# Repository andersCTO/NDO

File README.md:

# NDO

## Installation for development
1. Create a ROS2 workspace or use [NDO workspace for VSCode](https://github.com/JPDF/vscode_ndo_ros2_ws).
2. Copy this repo to your workspace. Your workspace should now look like this:
```
workspace
└──src
    └──ndo <-- THIS REPO
       │  README.md
       │  ...
       └──ndo
       └──ndo_description
       └──ndo_nav
       └──ndo_teleop
```
3. Install dependencies `rosdep install --from-paths src --ignore-src -y`
4. Build project `colcon build`

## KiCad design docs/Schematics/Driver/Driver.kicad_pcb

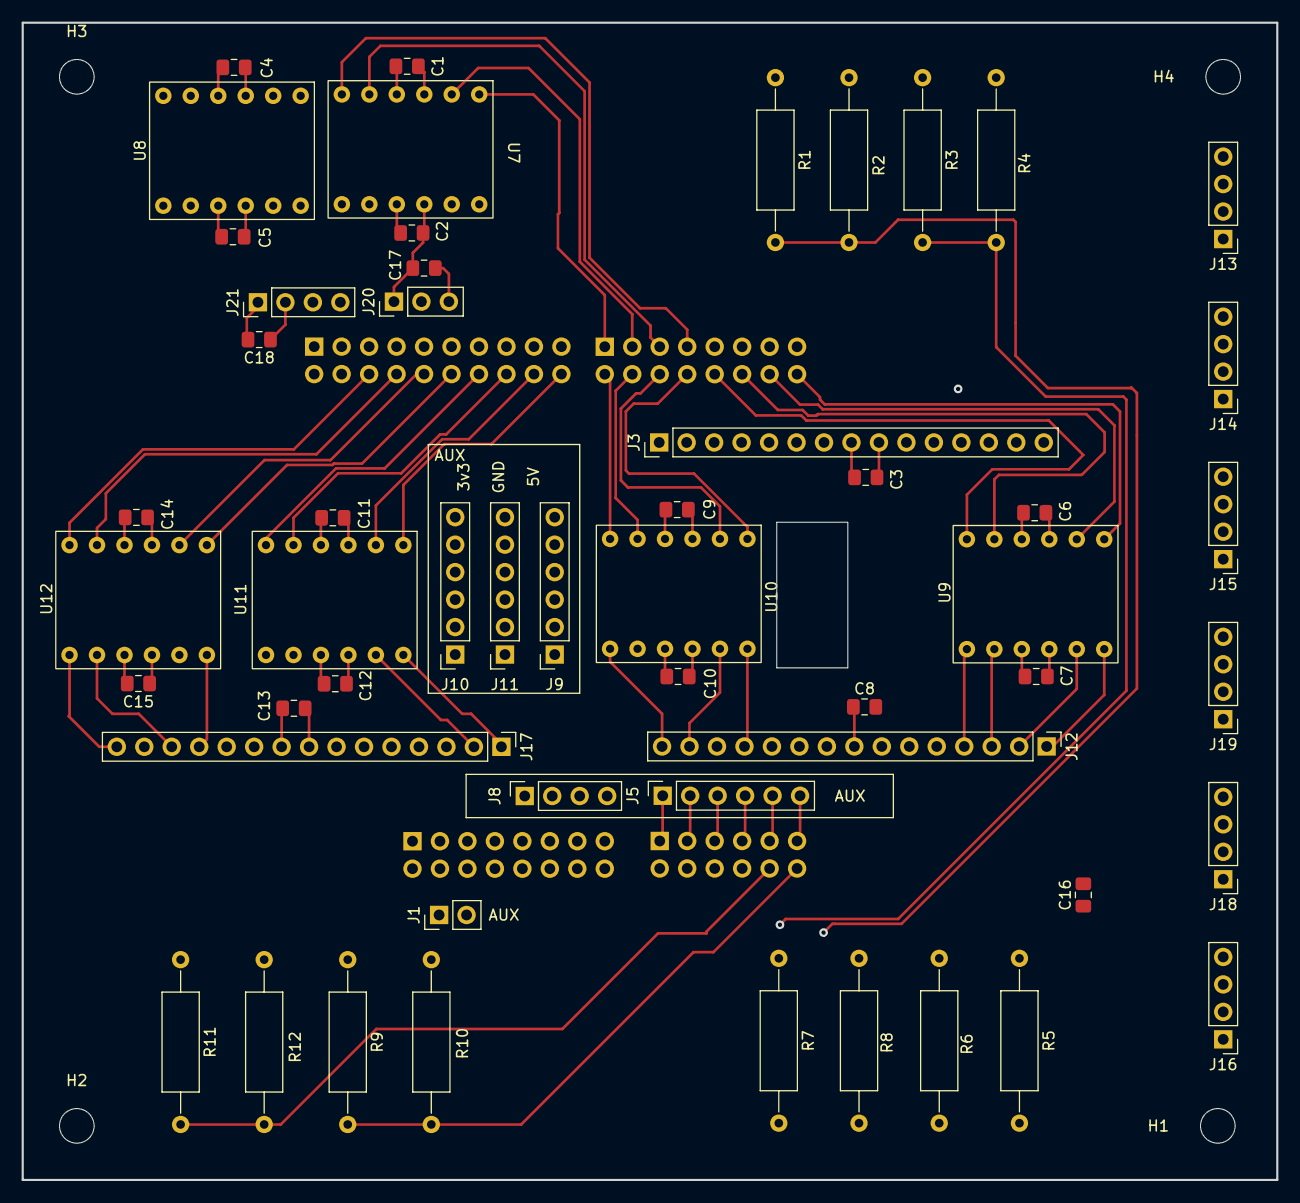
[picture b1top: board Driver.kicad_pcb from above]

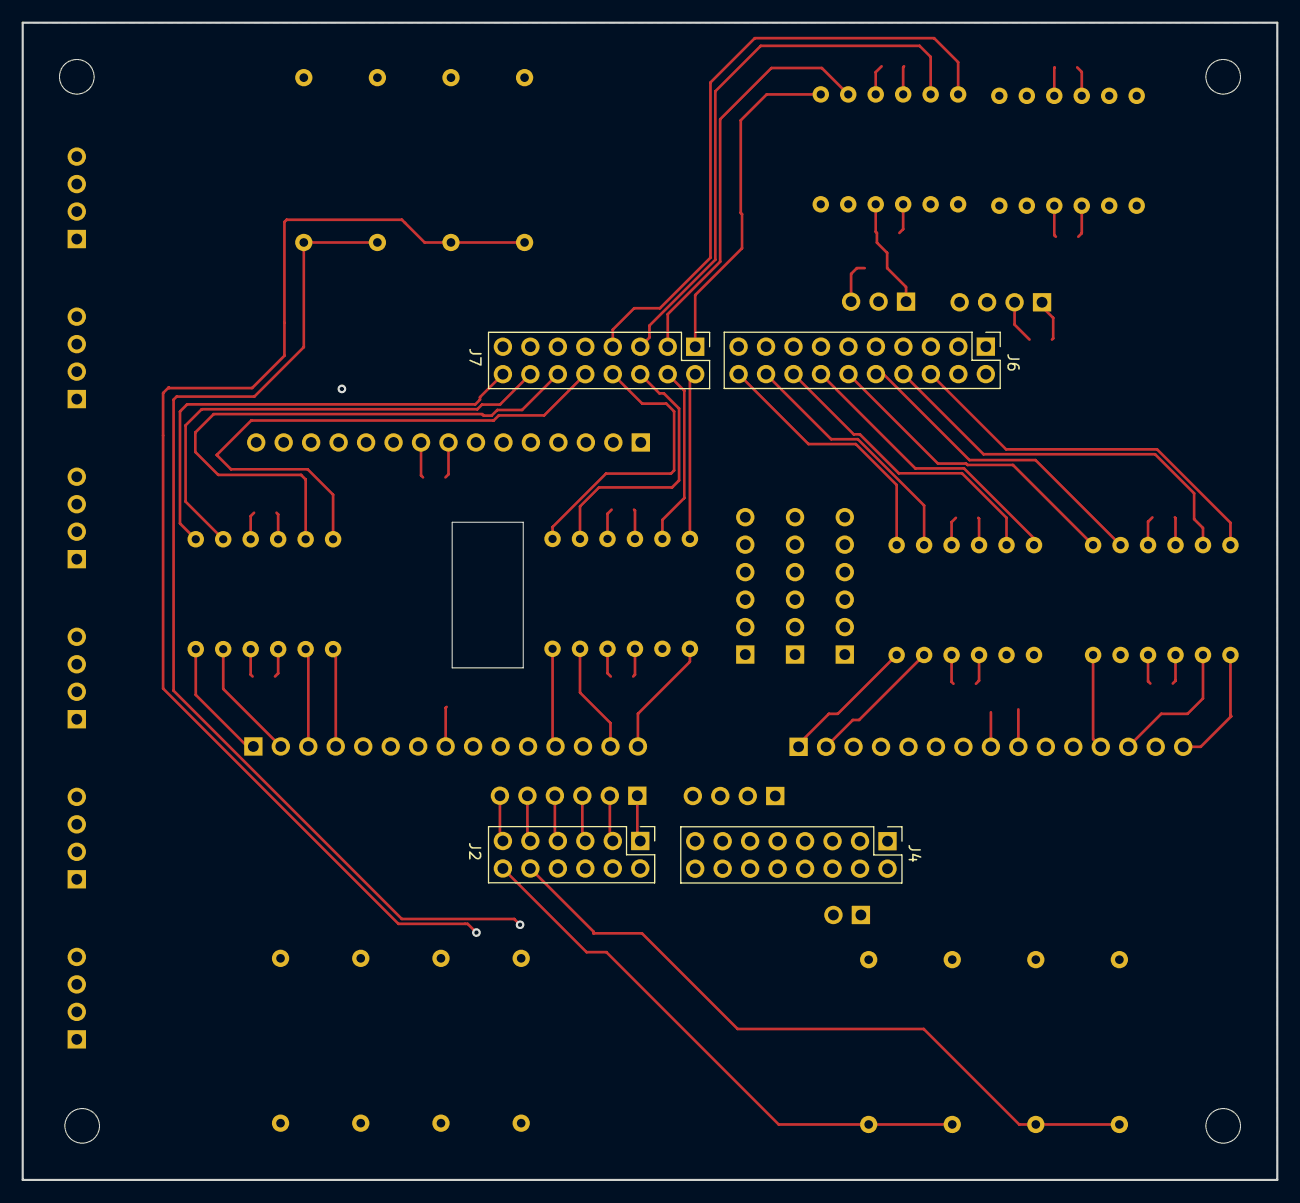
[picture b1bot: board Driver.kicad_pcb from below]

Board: 4 copper layers, 116.0 x 107.0 mm, 61 parts (4 on the bottom side), 83 nets.

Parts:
C1, C2, C3, C4, C5, C6, C7, C8, C9, C10, C11, C12, C13, C14, C15, C16, C17, C18: C_Polarized; C_0805_2012Metric_Pad1.18x1.45mm_HandSolder
H1, H2, H3, H4: MountingHole; MountingHole_3.2mm_M3
J1: AUX_IOref; PinHeader_1x02_P2.54mm_Vertical
J2: PH_Ain; PinHeader_2x06_P2.54mm_Vertical
J3, J12, J17: PH_MC; PinHeader_1x15_P2.54mm_Vertical
J4: PH_PWR; PinHeader_2x08_P2.54mm_Vertical
J5: AUX_AIO; PinSocket_1x06_P2.54mm_Vertical
J6: PH_IO1; PinHeader_2x10_P2.54mm_Vertical
J7: PH_IO2; PinHeader_2x08_P2.54mm_Vertical
J8: AUX_Ain; PinSocket_1x04_P2.54mm_Vertical
J9: AUX_5V; PinSocket_1x06_P2.54mm_Vertical
J10: AUX_3V3; PinSocket_1x06_P2.54mm_Vertical
J11: AUX_GND; PinSocket_1x06_P2.54mm_Vertical
J13: A1363xKTTN-1_front_left; PinHeader_1x04_P2.54mm_Vertical
J14: A1363xKTTN-1_midle_left; PinHeader_1x04_P2.54mm_Vertical
J15: A1363xKTTN-1_rear_left; PinHeader_1x04_P2.54mm_Vertical
J16: A1363xKTTN-1_front_right; PinHeader_1x04_P2.54mm_Vertical
J18: A1363xKTTN-1_midle_right; PinHeader_1x04_P2.54mm_Vertical
J19: A1363xKTTN-1_rear_right; PinHeader_1x04_P2.54mm_Vertical
J20: PH_HBT; PinHeader_1x03_P2.54mm_Vertical
J21: PH_I2C; PinHeader_1x04_P2.54mm_Vertical
R1, R2, R3, R4, R5, R6, R7, R8, R9, R10, R11, R12: R; R_Axial_DIN0309_L9.0mm_D3.2mm_P15.24mm_Horizontal
U7, U8, U9, U10, U11, U12: 4_channel_lvl_converter_Art.nr:_41017630; 4ch_level_shifter_Artnr_ 41017630

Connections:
+3.3V: C1.1, C4.1, C6.1, C9.1, C11.1, C14.1, C16.1, J4.8, J10.1, J10.2, J10.3, J10.4, J10.5, J10.6, J13.1, J14.1, J15.1, J16.1, J18.1, J19.1, U7.3 (3v3), U8.3 (3v3), U9.3 (3v3), U10.3 (3v3), U11.3 (3v3), U12.3 (3v3)
+5V: C2.1, C3.1, C5.1, C7.1, C8.1, C10.1, C12.1, C13.1, C15.1, C17.1, C18.1, J3.8, J4.10, J9.1, J9.2, J9.3, J9.4, J9.5, J9.6, J12.8, J17.8, J20.1, J21.2, U7.10 (5V), U8.10 (5V), U9.10 (5V), U10.10 (5V), U11.10 (5V), U12.10 (5V)
/Arty Z7/IOREF: J1.1, J4.4
/Arty Z7/RST: J1.2, J4.6
/Arty Z7/XVREF: J4.15, J8.4
/Arty Z7/v_n: J4.11, J8.2
/Arty Z7/v_p: J4.9, J8.1
/FLENC: J6.19, J13.2
/FRENC: J6.17, J16.2
/HeartBeat: J6.5, J20.2
/MFL/CS: J2.2, R1.2, R2.1
/MFL/EN: J7.1, U7.1 (LV1)
/MFL/INA: J7.3, U7.2 (LV2)
/MFL/INB: J7.5, U7.5 (LV3)
/MFL/PWM: J7.7, U7.6 (LV4)
/MFR/CS: J2.4, R3.2, R4.1
/MFR/EN: J7.15, U8.6 (LV4)
/MFR/INA: J7.13, U8.5 (LV3)
/MFR/INB: J7.11, U8.2 (LV2)
/MFR/PWM: J7.9, U8.1 (LV1)
/MLENC: J6.15, J14.2
/MML/EN: J7.16, U9.1 (LV1)
/MML/INA: J7.14, U9.2 (LV2)
/MML/INB: J7.12, U9.5 (LV3)
/MML/PWM: J7.10, U9.6 (LV4)
/MMR/CS: J2.6, R7.2, R8.1
/MMR/EN: J7.2, U10.6 (LV4)
/MMR/INA: J7.4, U10.5 (LV3)
/MMR/INB: J7.6, U10.2 (LV2)
/MMR/PWM: J7.8, U10.1 (LV1)
/MRENC: J6.13, J18.2
/MRL/CS: J2.12, R9.2, R10.1
/MRL/EN: J6.20, U11.1 (LV1)
/MRL/INA: J6.18, U11.2 (LV2)
/MRL/INB: J6.16, U11.5 (LV3)
/MRL/PWM: J6.14, U11.6 (LV4)
/MRR/CS: J2.10, R11.2, R12.1
/MRR/EN: J6.6, U12.6 (LV4)
/MRR/INB: J6.10, U12.2 (LV2)
/MRR/PWM: J6.12, U12.1 (LV1)
/MR/INA: J6.8, U12.5 (LV3)
/MWL/CS: J2.8, R5.2, R6.1
/Motor Driver Front/Dual_VNH3SP30/1CS: J3.5, R1.1
/Motor Driver Front/Dual_VNH3SP30/1DIAG/EN: J3.1, U7.12 (HV1)
/Motor Driver Front/Dual_VNH3SP30/1INA: J3.2, U7.11 (HV2)
/Motor Driver Front/Dual_VNH3SP30/1INB: J3.3, U7.8 (HV3)
/Motor Driver Front/Dual_VNH3SP30/1PWM: J3.4, U7.7 (HV4)
/Motor Driver Front/Dual_VNH3SP30/2CS: J3.11, R3.1
/Motor Driver Front/Dual_VNH3SP30/2DIAG/EN: J3.15, U8.7 (HV4)
/Motor Driver Front/Dual_VNH3SP30/2INA: J3.13, U8.8 (HV3)
/Motor Driver Front/Dual_VNH3SP30/2INB: J3.14, U8.11 (HV2)
/Motor Driver Front/Dual_VNH3SP30/2PWM: J3.12, U8.12 (HV1)
/Motor Driver Midle/Dual_VNH3SP30/1CS: J12.5, R5.1
/Motor Driver Midle/Dual_VNH3SP30/1DIAG/EN: J12.1, U9.12 (HV1)
/Motor Driver Midle/Dual_VNH3SP30/1INA: J12.2, U9.11 (HV2)
/Motor Driver Midle/Dual_VNH3SP30/1INB: J12.3, U9.8 (HV3)
/Motor Driver Midle/Dual_VNH3SP30/1PWM: J12.4, U9.7 (HV4)
/Motor Driver Midle/Dual_VNH3SP30/2CS: J12.11, R7.1
/Motor Driver Midle/Dual_VNH3SP30/2DIAG/EN: J12.15, U10.7 (HV4)
/Motor Driver Midle/Dual_VNH3SP30/2INA: J12.13, U10.8 (HV3)
/Motor Driver Midle/Dual_VNH3SP30/2INB: J12.14, U10.11 (HV2)
/Motor Driver Midle/Dual_VNH3SP30/2PWM: J12.12, U10.12 (HV1)
/Motor Driver Rear/Dual_VNH3SP30/1CS: J17.5, R9.1
/Motor Driver Rear/Dual_VNH3SP30/1DIAG/EN: J17.1, U11.12 (HV1)
/Motor Driver Rear/Dual_VNH3SP30/1INA: J17.2, U11.11 (HV2)
/Motor Driver Rear/Dual_VNH3SP30/1INB: J17.3, U11.8 (HV3)
/Motor Driver Rear/Dual_VNH3SP30/1PWM: J17.4, U11.7 (HV4)
/Motor Driver Rear/Dual_VNH3SP30/2CS: J17.11, R11.1
/Motor Driver Rear/Dual_VNH3SP30/2DIAG/EN: J17.15, U12.7 (HV4)
/Motor Driver Rear/Dual_VNH3SP30/2INA: J17.13, U12.8 (HV3)
/Motor Driver Rear/Dual_VNH3SP30/2INB: J17.14, U12.11 (HV2)
/Motor Driver Rear/Dual_VNH3SP30/2PWM: J17.12, U12.12 (HV1)
/RLENC: J6.11, J15.2
/RRENC: J6.9, J19.2
/SCL: J6.1, J21.3
/SDA: J6.3, J21.4
GNDD: C1.2, C2.2, C3.2, C4.2, C5.2, C6.2, C7.2, C8.2, C9.2, C10.2, C11.2, C12.2, C13.2, C14.2, C15.2, C16.2, C17.2, C18.2, J3.7, J3.9, J4.12, J4.13, J4.14, J6.7, J8.3, J11.1, J11.2, J11.3, J11.4, J11.5, J11.6, J12.7, J12.9, J13.4, J14.4, J15.4, J16.4, J17.7, J17.9, J18.4, J19.4, J20.3, J21.1, R2.2, R4.2, R6.2, R8.2, R10.2, R12.2, U7.4 (LVGND), U7.9 (HVGND), U8.4 (LVGND), U8.9 (HVGND), U9.4 (LVGND), U9.9 (HVGND), U10.4 (LVGND), U10.9 (HVGND), U11.4 (LVGND), U11.9 (HVGND), U12.4 (LVGND), U12.9 (HVGND)
unnamed: J2.1, J5.1
unnamed: J2.3, J5.2
unnamed: J2.5, J5.3
unnamed: J2.7, J5.4
unnamed: J2.9, J5.5
unnamed: J2.11, J5.6

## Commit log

2022-11-23 Add dir structure and start of driver schematic
2022-11-23 Add Wheel encoder
2022-11-24 Added esp32HB and oled
2022-12-24 First scematic design for the card
2022-12-25 Added footprints and a symbol for the level shifters
2022-12-25 Added caps and changed the connection from the motor sensors to plints
2022-12-26 Started routing the pcb.
2022-12-27 Changed a few nets to make the routing posible
2022-12-27 First version of the routed board is done
2022-12-28 First version sent to fab
2022-12-29 Revision 1.0 re uploaded to JLCPCB
2023-01-15 Added freecad_model of the driver card to the repo
2023-02-08 Init ndo package
2023-02-08 Init ndo_teleop package
2023-02-09 Init ndo_description package
2023-02-09 Init ndo_nav package
2023-02-10 hotfix teleop dependency
2023-02-17 Add mesh model to urdf
2023-02-21 Add gazebo config and ros2_controller
2023-02-21 Fixed controllers
2023-02-21 Add dummy link to enable inertia for the body
2023-02-22 Update mesh and inertia
2023-02-22 Update controllers
2023-02-22 Spawn controllers in certain order
2023-02-22 Reorder links base_footprint -> base_link
2023-02-22 Improved inertia calculation
2023-02-22 Refactor urdf
2023-02-22 Refactor to ndo_gazebo
2023-02-27 add robot localization
2023-02-27 tweak localization config
2023-02-27 Add dependency to package.xml
